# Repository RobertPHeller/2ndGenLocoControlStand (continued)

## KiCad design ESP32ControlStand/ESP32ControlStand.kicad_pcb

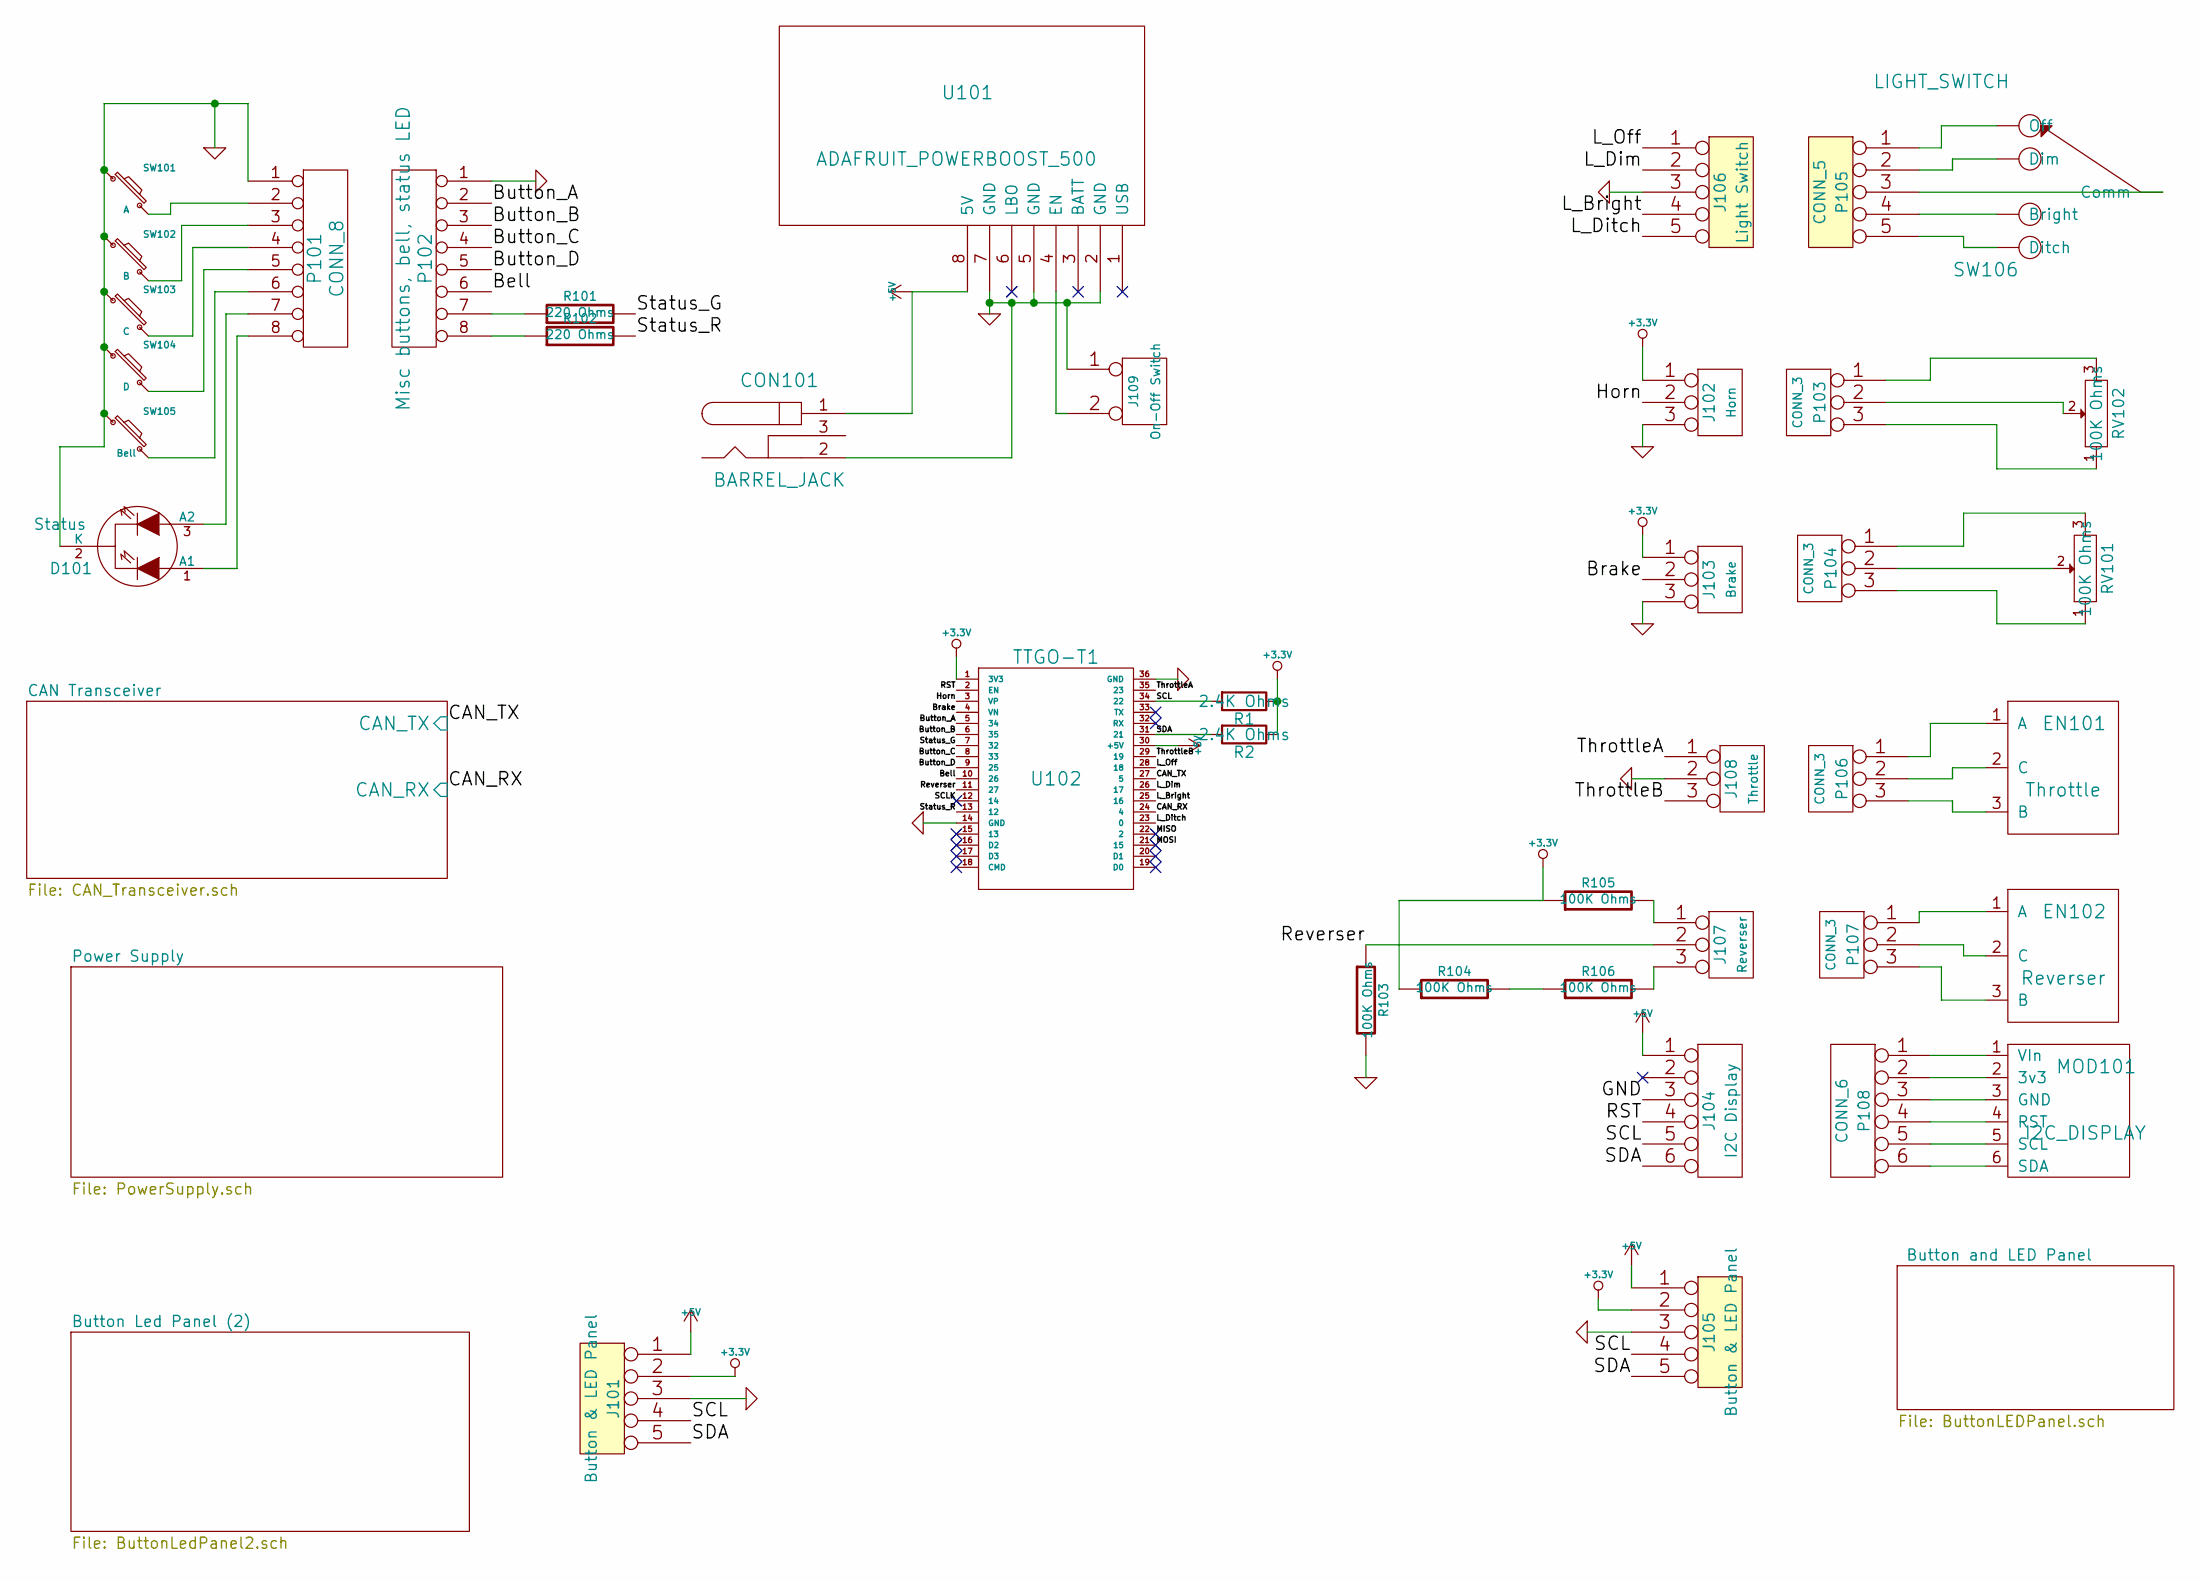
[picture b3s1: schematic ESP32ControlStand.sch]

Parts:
CON101: BARREL_JACK
D101: Status
EN101: Throttle; Mouser Part Number 706-25LB10-Q
EN102: Reverser; Mouser Part Number 652-PEC11R4325FN0012
J101, J105: Button & LED Panel
J102: Horn
J103: Brake
J104: I2C Display
J106: Light Switch
J107: Reverser
J108: Throttle
J109: On-Off Switch
MOD101: I2C_DISPLAY
P101: CONN_8
P102: Misc buttons, bell, status LED
P103, P104, P106, P107: CONN_3
P105: CONN_5
P108: CONN_6
R1, R2: 2.4K Ohms; R_Axial_DIN0207_L6.3mm_D2.5mm_P2.54mm_Vertical
R101, R102: 220 Ohms
R103, R104, R105, R106: 100K Ohms
RV101, RV102: 100K Ohms; Mouser Part Number 774-450T328F104A1A1
SW101: A
SW102: B
SW103: C
SW104: D
SW105: Bell
SW106: LIGHT_SWITCH
U101: ADAFRUIT_POWERBOOST_500
U102: TTGO-T1

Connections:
+3.3V: J101.2, J102.1, J103.1, J105.2, R1.1, R2.1, R104.1, R105.1, U102.1 (3V3); also elsewhere on the board
+5V: CON101.1, J101.1, J104.1, J105.1, U101.8 (5V), U102.30 (+5V); also elsewhere on the board
/Bell: P102.6, U102.10 (26)
/Brake: J103.2 (PM), U102.4 (VN)
/Button_A: P102.2, U102.5 (34)
/Button_B: P102.3, U102.6 (35)
/Button_C: P102.4, U102.8 (33)
/Button_D: P102.5, U102.9 (25)
/CAN_RX: U102.24 (4); also elsewhere on the board
/CAN_TX: U102.27 (5); also elsewhere on the board
/Horn: J102.2 (PM), U102.3 (VP)
/L_Bright: J106.4, U102.25 (16)
/L_Dim: J106.2, U102.26 (17)
/L_Ditch: J106.5, U102.23 (0)
/L_Off: J106.1, U102.28 (18)
/MISO: U102.22 (2)
/MOSI: U102.21 (15)
/RST: J104.4, U102.2 (EN)
/Reverser: J107.2 (PM), R103.1, U102.11 (27)
/SCL: J101.4, J104.5, J105.4, R1.2, U102.34 (22)
/SCLK: U102.12 (14)
/SDA: J101.5, J104.6, J105.5, R2.2, U102.31 (21)
/Status_G: R101.2, U102.7 (32)
/Status_R: R102.2, U102.13 (12)
/ThrottleA: J108.1, U102.35 (23)
/ThrottleB: J108.3, U102.29 (19)
GND: CON101.2, D101.2 (K), J101.3, J102.3, J103.3, J104.3, J105.3, J106.3, J108.2 (PM), J109.1, P101.1, P102.1, R103.2, SW101.1, SW102.1, SW103.1, SW104.1, SW105.1, U101.2 (GND), U101.5 (GND), U101.7 (GND), U102.14 (GND), U102.36 (GND); also elsewhere on the board
unnamed: D101.1 (A1), P101.8
unnamed: D101.3 (A2), P101.7
unnamed: EN101.1 (A), P106.1
unnamed: EN101.2 (C), P106.2 (PM)
unnamed: EN101.3 (B), P106.3
unnamed: EN102.1 (A), P107.1
unnamed: EN102.2 (C), P107.2 (PM)
unnamed: EN102.3 (B), P107.3
unnamed: J107.1, R105.2
unnamed: J107.3, R106.2
unnamed: J109.2 (PM), U101.4 (EN)
unnamed: MOD101.1 (VIn), P108.1
unnamed: MOD101.2 (3v3), P108.2
unnamed: MOD101.3 (GND), P108.3
unnamed: MOD101.4 (RST), P108.4
unnamed: MOD101.5 (SCL), P108.5
unnamed: MOD101.6 (SDA), P108.6
unnamed: P101.2, SW101.2
unnamed: P101.3, SW102.2
unnamed: P101.4, SW103.2
unnamed: P101.5, SW104.2
unnamed: P101.6, SW105.2
unnamed: P102.7, R101.1
unnamed: P102.8, R102.1
unnamed: P103.1, RV102.3
unnamed: P103.2 (PM), RV102.2
unnamed: P103.3, RV102.1
unnamed: P104.1, RV101.3
unnamed: P104.2 (PM), RV101.2
unnamed: P104.3, RV101.1
unnamed: P105.1, SW106.~
unnamed: P105.2, SW106.~
unnamed: P105.3, SW106.~
unnamed: P105.4, SW106.~
unnamed: P105.5, SW106.~
unnamed: R104.2, R106.1

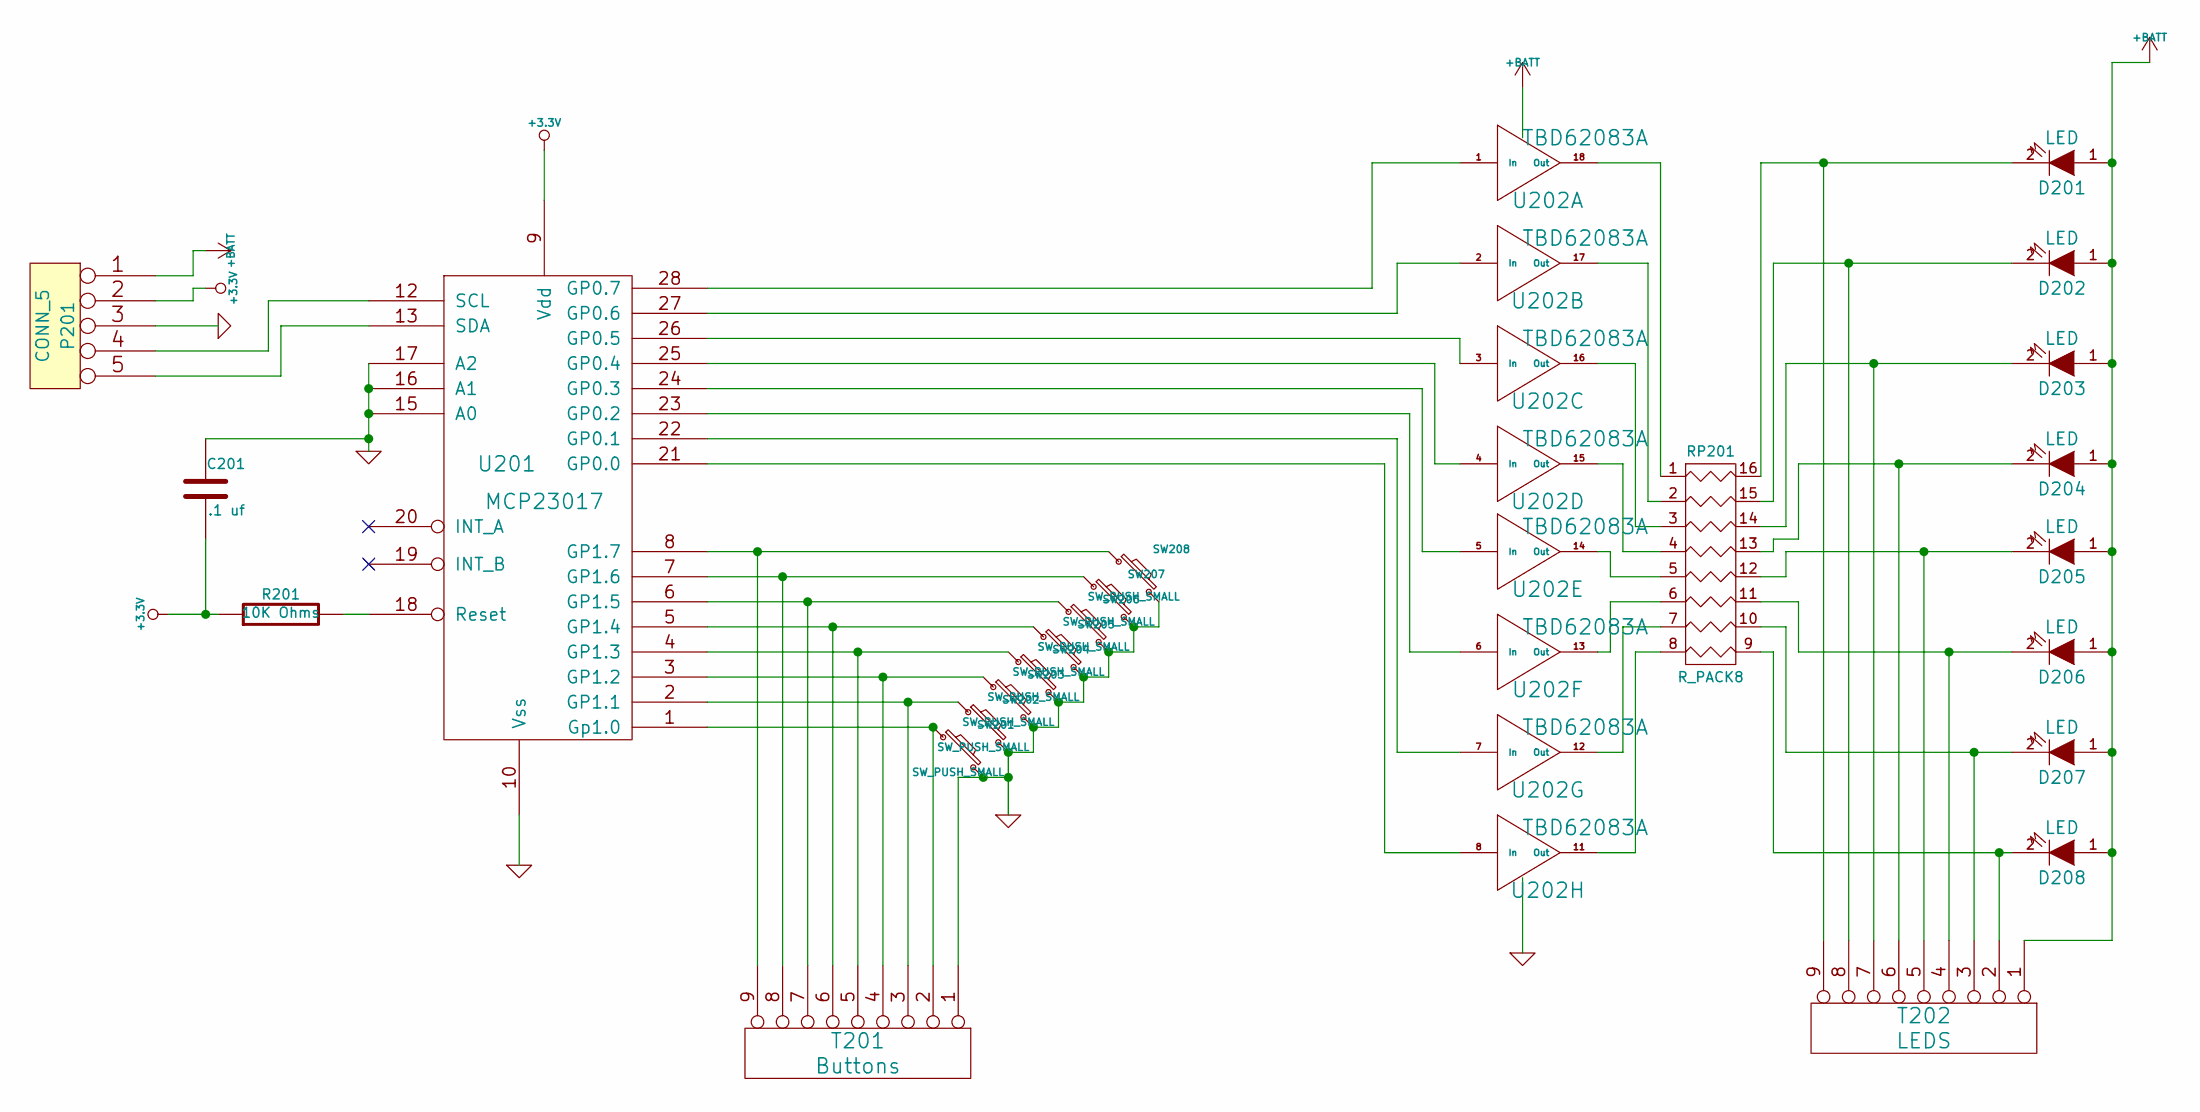
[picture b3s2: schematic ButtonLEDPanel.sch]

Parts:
C201: .1 uf
D201, D202, D203, D204, D205, D206, D207, D208: LED
P201: CONN_5
R201: 10K Ohms
RP201: R_PACK8
SW201, SW202, SW203, SW204, SW205, SW206, SW207, SW208: SW_PUSH_SMALL
T201: Buttons
T202: LEDS
U201: MCP23017
U202: TBD62083A

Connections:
+3.3V: C201.2, P201.2, R201.1, U201.9 (Vdd); also elsewhere on the board
+BATT: D201.1 (A), D202.1 (A), D203.1 (A), D204.1 (A), D205.1 (A), D206.1 (A), D207.1 (A), D208.1 (A), P201.1, T202.1, U202.10 (OC); also elsewhere on the board
GND: C201.1, P201.3, SW201.2, SW202.2, SW203.2, SW204.2, SW205.2, SW206.2, SW207.2, SW208.2, T201.1, U201.10 (Vss), U201.15 (A0), U201.16 (A1), U201.17 (A2), U202.9 (IC); also elsewhere on the board
unnamed: D201.2 (K), RP201.16 (R1), T202.9
unnamed: D202.2 (K), RP201.15 (R2), T202.8
unnamed: D203.2 (K), RP201.14 (R3), T202.7
unnamed: D204.2 (K), RP201.13 (R4), T202.6
unnamed: D205.2 (K), RP201.12 (R5), T202.5
unnamed: D206.2 (K), RP201.11 (R6), T202.4
unnamed: D207.2 (K), RP201.10 (R7), T202.3
unnamed: D208.2 (K), RP201.9 (R8), T202.2
unnamed: P201.4, U201.12 (SCL)
unnamed: P201.5, U201.13 (SDA)
unnamed: R201.2, U201.18 (Reset)
unnamed: RP201.1, U202.18 (Out)
unnamed: RP201.2, U202.17 (Out)
unnamed: RP201.3, U202.16 (Out)
unnamed: RP201.4, U202.15 (Out)
unnamed: RP201.5, U202.14 (Out)
unnamed: RP201.6, U202.13 (Out)
unnamed: RP201.7, U202.12 (Out)
unnamed: RP201.8, U202.11 (Out)
unnamed: SW201.1, T201.2, U201.1 (Gp1.0)
unnamed: SW202.1, T201.3, U201.2 (GP1.1)
unnamed: SW203.1, T201.4, U201.3 (GP1.2)
unnamed: SW204.1, T201.5, U201.4 (GP1.3)
unnamed: SW205.1, T201.6, U201.5 (GP1.4)
unnamed: SW206.1, T201.7, U201.6 (GP1.5)
unnamed: SW207.1, T201.8, U201.7 (GP1.6)
unnamed: SW208.1, T201.9, U201.8 (GP1.7)
unnamed: U201.21 (GP0.0), U202.8 (In)
unnamed: U201.22 (GP0.1), U202.7 (In)
unnamed: U201.23 (GP0.2), U202.6 (In)
unnamed: U201.24 (GP0.3), U202.5 (In)
unnamed: U201.25 (GP0.4), U202.4 (In)
unnamed: U201.26 (GP0.5), U202.3 (In)
unnamed: U201.27 (GP0.6), U202.2 (In)
unnamed: U201.28 (GP0.7), U202.1 (In)

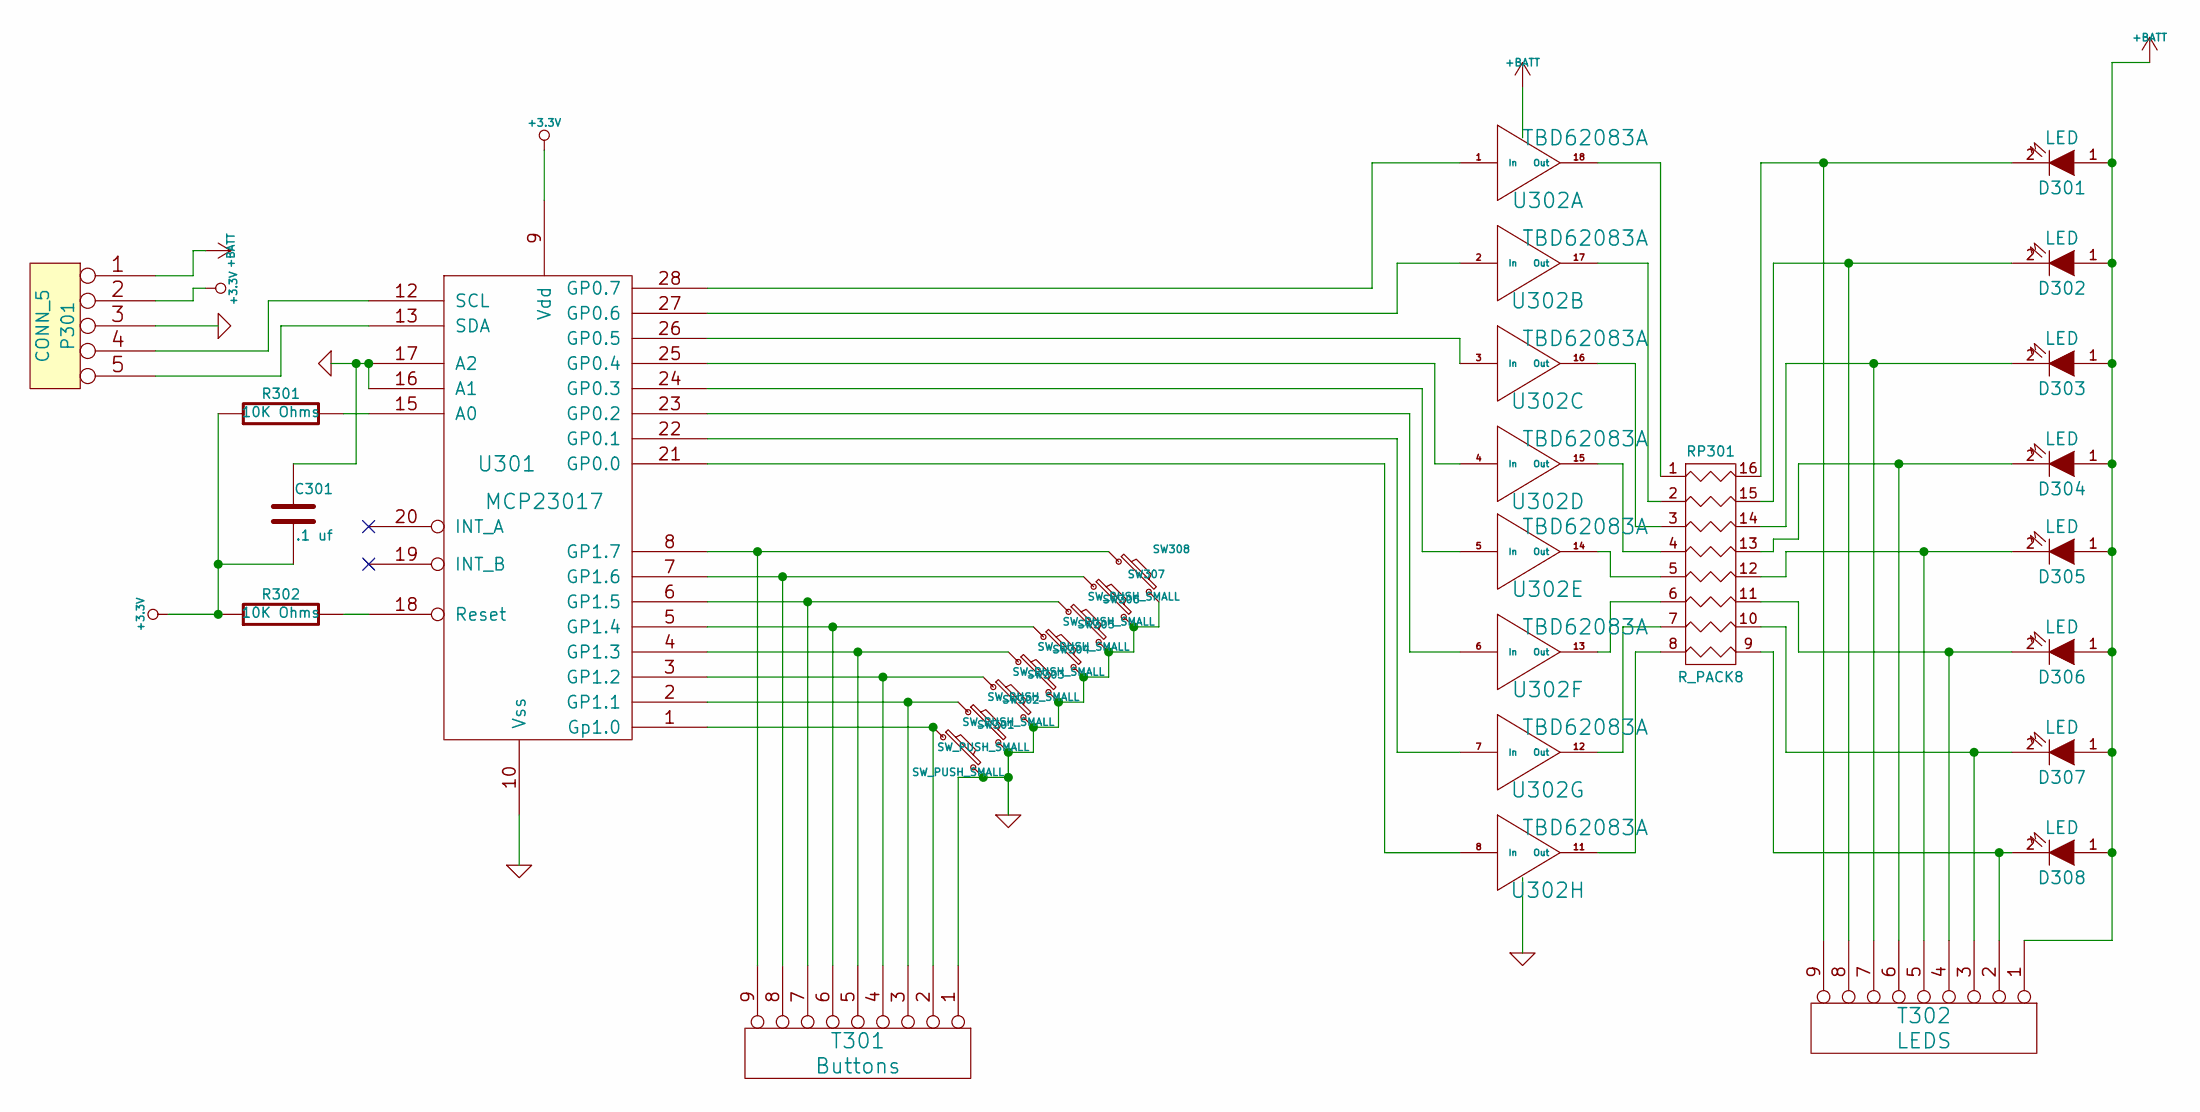
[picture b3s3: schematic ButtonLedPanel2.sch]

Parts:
C301: .1 uf
D301, D302, D303, D304, D305, D306, D307, D308: LED
P301: CONN_5
R301, R302: 10K Ohms
RP301: R_PACK8
SW301, SW302, SW303, SW304, SW305, SW306, SW307, SW308: SW_PUSH_SMALL
T301: Buttons
T302: LEDS
U301: MCP23017
U302: TBD62083A

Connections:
+3.3V: C301.2, P301.2, R301.1, R302.1, U301.9 (Vdd); also elsewhere on the board
+BATT: D301.1 (A), D302.1 (A), D303.1 (A), D304.1 (A), D305.1 (A), D306.1 (A), D307.1 (A), D308.1 (A), P301.1, T302.1, U302.10 (OC); also elsewhere on the board
GND: C301.1, P301.3, SW301.2, SW302.2, SW303.2, SW304.2, SW305.2, SW306.2, SW307.2, SW308.2, T301.1, U301.10 (Vss), U301.16 (A1), U301.17 (A2), U302.9 (IC); also elsewhere on the board
unnamed: D301.2 (K), RP301.16 (R1), T302.9
unnamed: D302.2 (K), RP301.15 (R2), T302.8
unnamed: D303.2 (K), RP301.14 (R3), T302.7
unnamed: D304.2 (K), RP301.13 (R4), T302.6
unnamed: D305.2 (K), RP301.12 (R5), T302.5
unnamed: D306.2 (K), RP301.11 (R6), T302.4
unnamed: D307.2 (K), RP301.10 (R7), T302.3
unnamed: D308.2 (K), RP301.9 (R8), T302.2
unnamed: P301.4, U301.12 (SCL)
unnamed: P301.5, U301.13 (SDA)
unnamed: R301.2, U301.15 (A0)
unnamed: R302.2, U301.18 (Reset)
unnamed: RP301.1, U302.18 (Out)
unnamed: RP301.2, U302.17 (Out)
unnamed: RP301.3, U302.16 (Out)
unnamed: RP301.4, U302.15 (Out)
unnamed: RP301.5, U302.14 (Out)
unnamed: RP301.6, U302.13 (Out)
unnamed: RP301.7, U302.12 (Out)
unnamed: RP301.8, U302.11 (Out)
unnamed: SW301.1, T301.2, U301.1 (Gp1.0)
unnamed: SW302.1, T301.3, U301.2 (GP1.1)
unnamed: SW303.1, T301.4, U301.3 (GP1.2)
unnamed: SW304.1, T301.5, U301.4 (GP1.3)
unnamed: SW305.1, T301.6, U301.5 (GP1.4)
unnamed: SW306.1, T301.7, U301.6 (GP1.5)
unnamed: SW307.1, T301.8, U301.7 (GP1.6)
unnamed: SW308.1, T301.9, U301.8 (GP1.7)
unnamed: U301.21 (GP0.0), U302.8 (In)
unnamed: U301.22 (GP0.1), U302.7 (In)
unnamed: U301.23 (GP0.2), U302.6 (In)
unnamed: U301.24 (GP0.3), U302.5 (In)
unnamed: U301.25 (GP0.4), U302.4 (In)
unnamed: U301.26 (GP0.5), U302.3 (In)
unnamed: U301.27 (GP0.6), U302.2 (In)
unnamed: U301.28 (GP0.7), U302.1 (In)

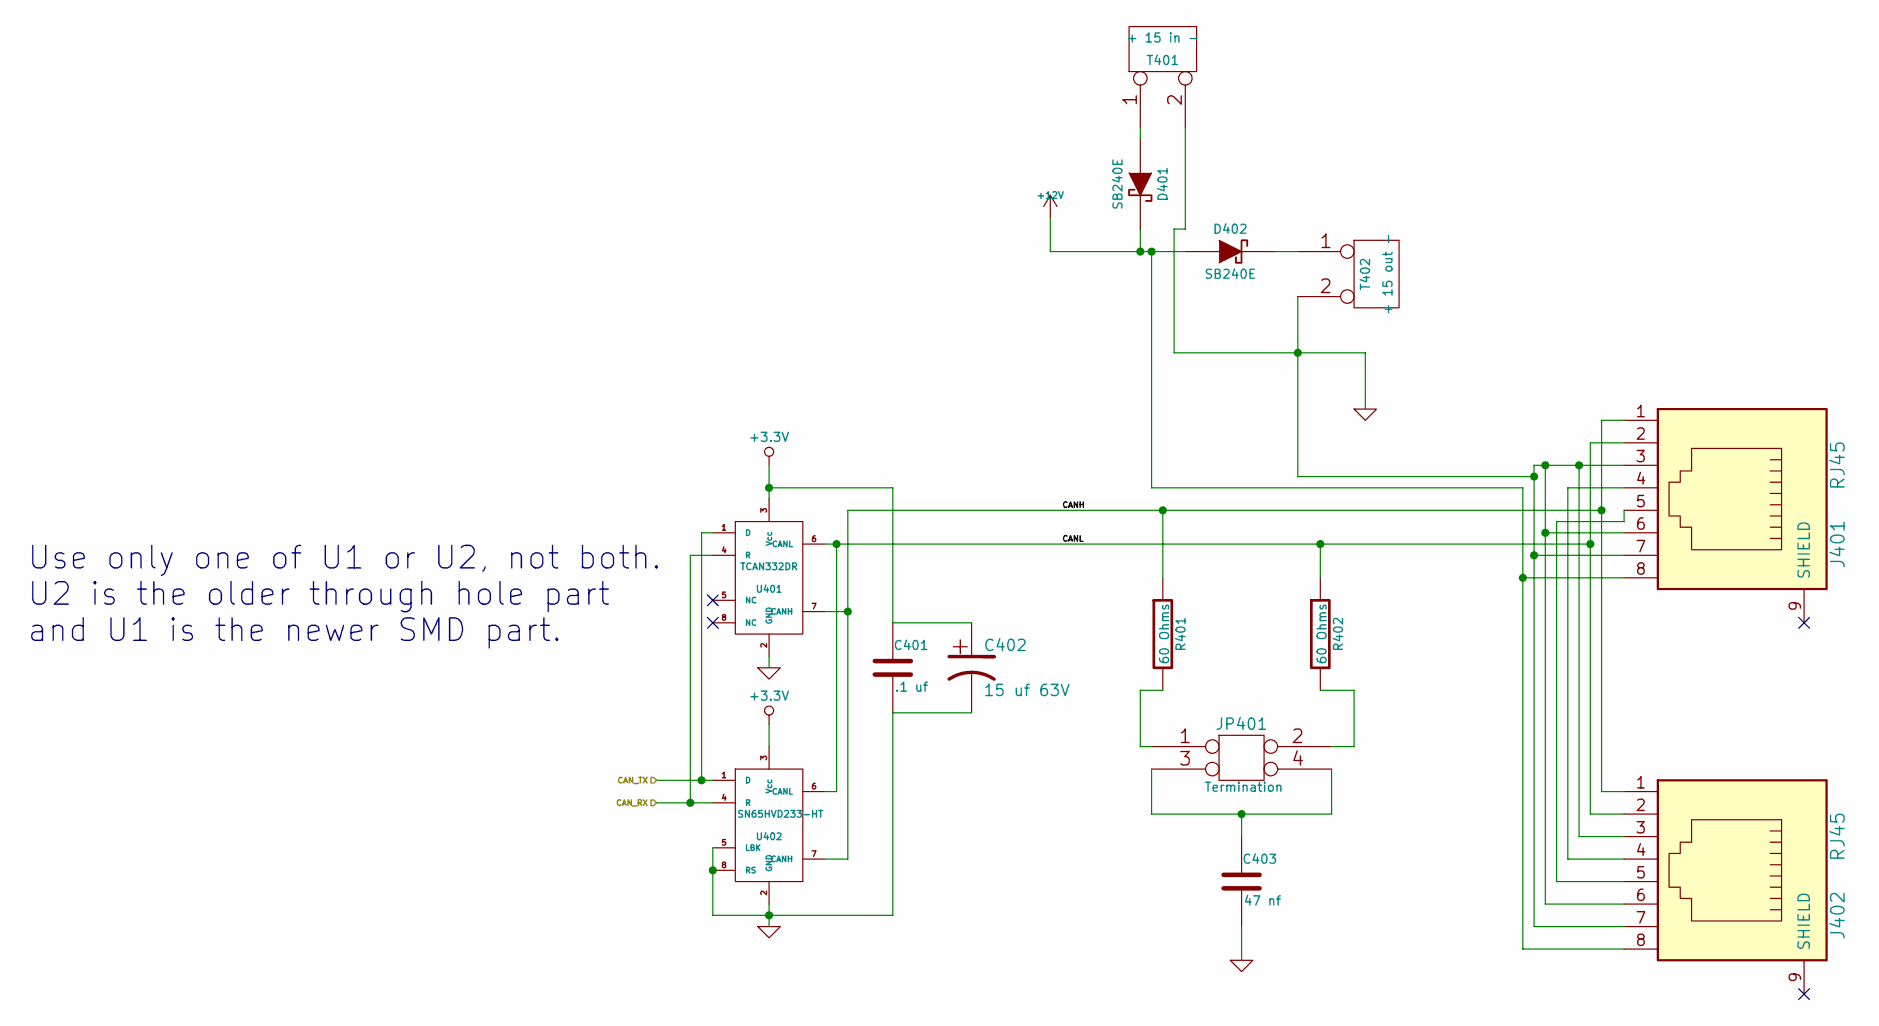
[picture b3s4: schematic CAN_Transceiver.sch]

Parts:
C401: .1 uf; Mouser Part Number 21RZ310-RC
C402: 15 uf 63V; Mouser Part Number 710-860080773002
C403: 47 nf; Mouser Part Number 75-1C10Z5U473M050B
D401, D402: SB240E; Mouser Part Number 625-SB240-E3
J401, J402: RJ45; Mouser Part Number 710-615008144221
JP401: Termination; Mouser Part Number 649-67997-404HLF
R401, R402: 60 Ohms; Mouser Part Number 71-RN60C60R0B/R
T401: + 15 in -; Mouser Part Number 651-1725656
T402: + 15 out -; Mouser Part Number 651-1725656
U401: TCAN332DR; Mouser Part Number 595-TCAN332DR
U402: SN65HVD233-HT; Mouser Part Number 595-SN65HVD233SJD

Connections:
+3.3V: C401.1, C402.1, U401.3 (Vcc), U402.3 (Vcc); also elsewhere on the board
+12V: D401.2 (K), D402.1 (A), J401.8, J402.8; also elsewhere on the board
/CAN Transceiver/CANH: J401.1, J402.1, R401.1, U401.7 (CANH), U402.7 (CANH)
/CAN Transceiver/CANL: J401.2, J402.2, R402.1, U401.6 (CANL), U402.6 (CANL)
/CAN_RX: U401.4 (R), U402.4 (R); also elsewhere on the board
/CAN_TX: U401.1 (D), U402.1 (D); also elsewhere on the board
GND: C401.2, C402.2, C403.2, J401.3, J401.6, J401.7, J402.3, J402.6, J402.7, T401.2 (PM), T402.2 (PM), U401.2 (GND), U402.2 (GND), U402.5 (LBK), U402.8 (RS); also elsewhere on the board
unnamed: C403.1, JP401.3, JP401.4
unnamed: D401.1 (A), T401.1
unnamed: D402.2 (K), T402.1
unnamed: J401.4, J402.4
unnamed: J401.5, J402.5
unnamed: JP401.1, R401.2
unnamed: JP401.2, R402.2

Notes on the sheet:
Use only one of U1 or U2, not both. U2 is the older through hole part and U1 is the newer SMD part.

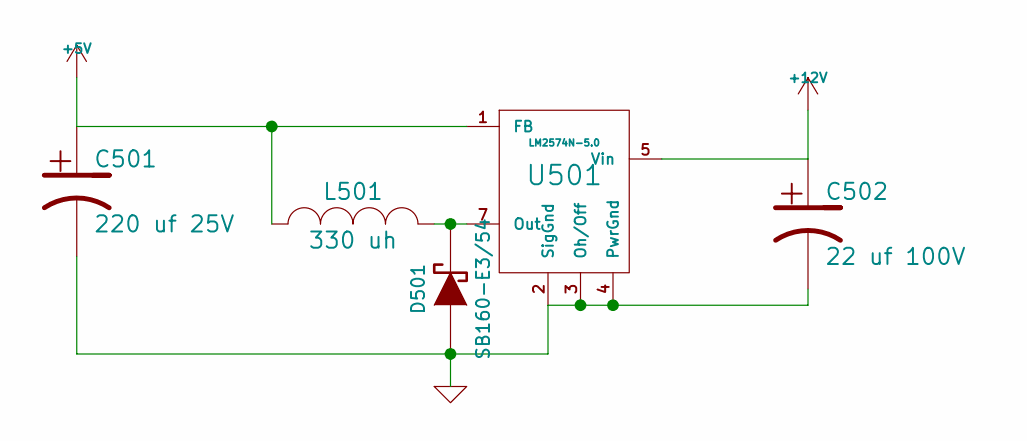
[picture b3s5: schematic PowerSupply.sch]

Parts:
C501: 220 uf 25V; Mouser Part Number 140-REA221M1EBK0811P
C502: 22 uf 100V; Mouser Part Number 140-REA220M2ABK0811P
D501: SB160-E3/54; Mouser Part Number 625-SB160-E3
L501: 330 uh; Mouser Part Number PE-52627NL
U501: LM2574N-5.0; Mouser Part Number 926-LM2574N-5.0/NOPB

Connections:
+5V: C501.1, L501.1, U501.1 (FB); also elsewhere on the board
+12V: C502.1, U501.5 (Vin); also elsewhere on the board
GND: C501.2, C502.2, D501.1 (A), U501.2 (SigGnd), U501.3 (Oh/Off), U501.4 (PwrGnd); also elsewhere on the board
unnamed: D501.2 (K), L501.2, U501.7 (Out)

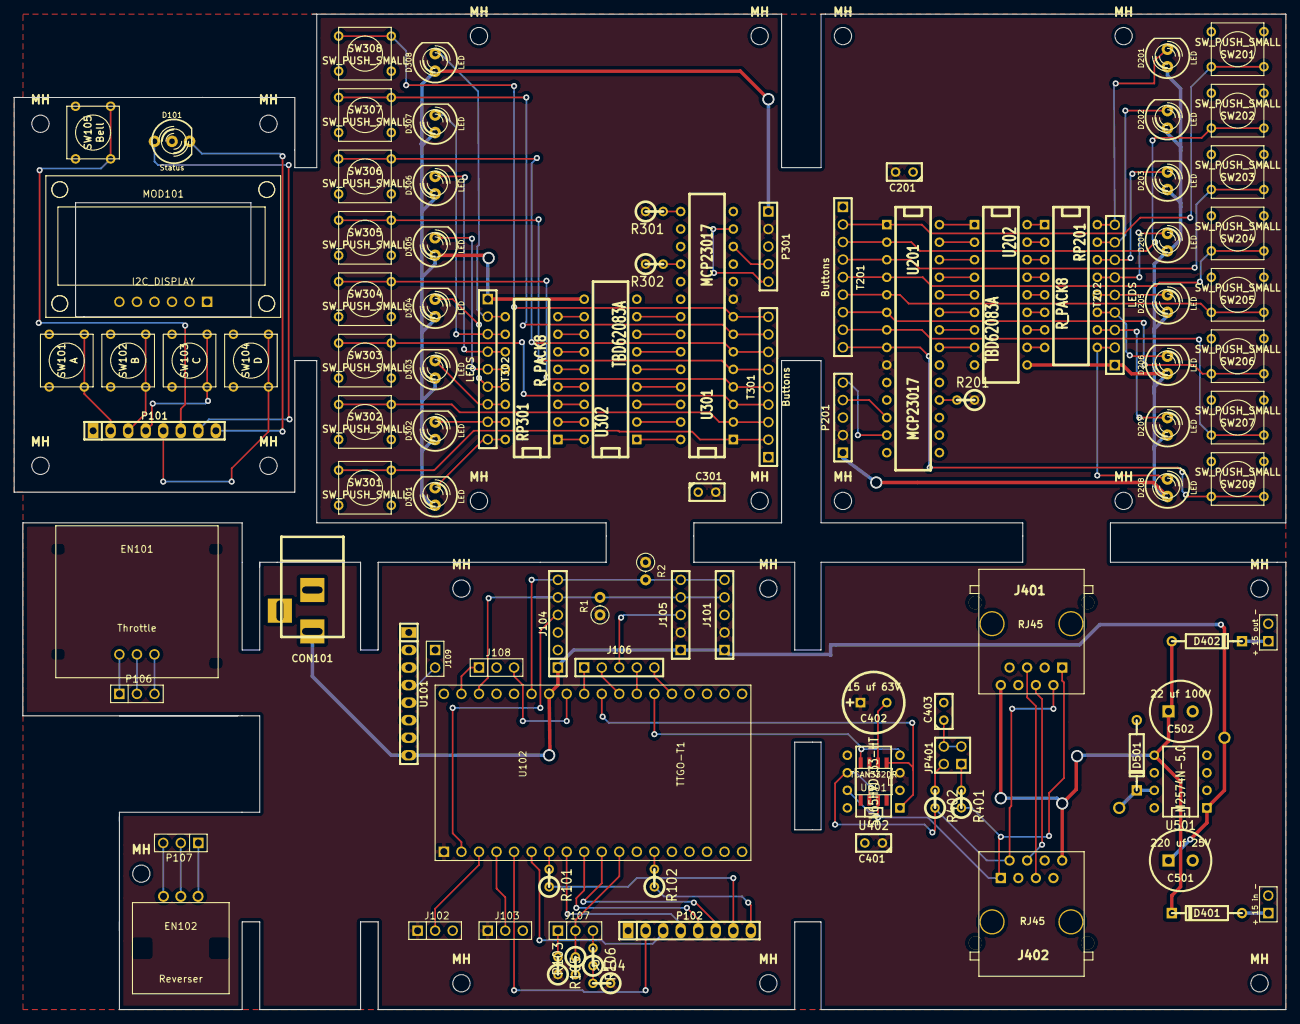
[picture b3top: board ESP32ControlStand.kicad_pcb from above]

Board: 2 copper layers, 184.1 x 144.1 mm, 120 parts (1 on the bottom side), 126 nets.

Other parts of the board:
MH: MountingHole_2-5mm_RevA_Date21Jun2010
MH#2, MH#3, MH#4, MH#5, MH#6, MH#7, MH#8, MH#9, MH#10, MH#11, MH#12, MH#13, MH#14, MH#15, MH#16, MH#17, MH#18, MH#19: MountingHole_2-5mm_RevA_Date21Jun2010

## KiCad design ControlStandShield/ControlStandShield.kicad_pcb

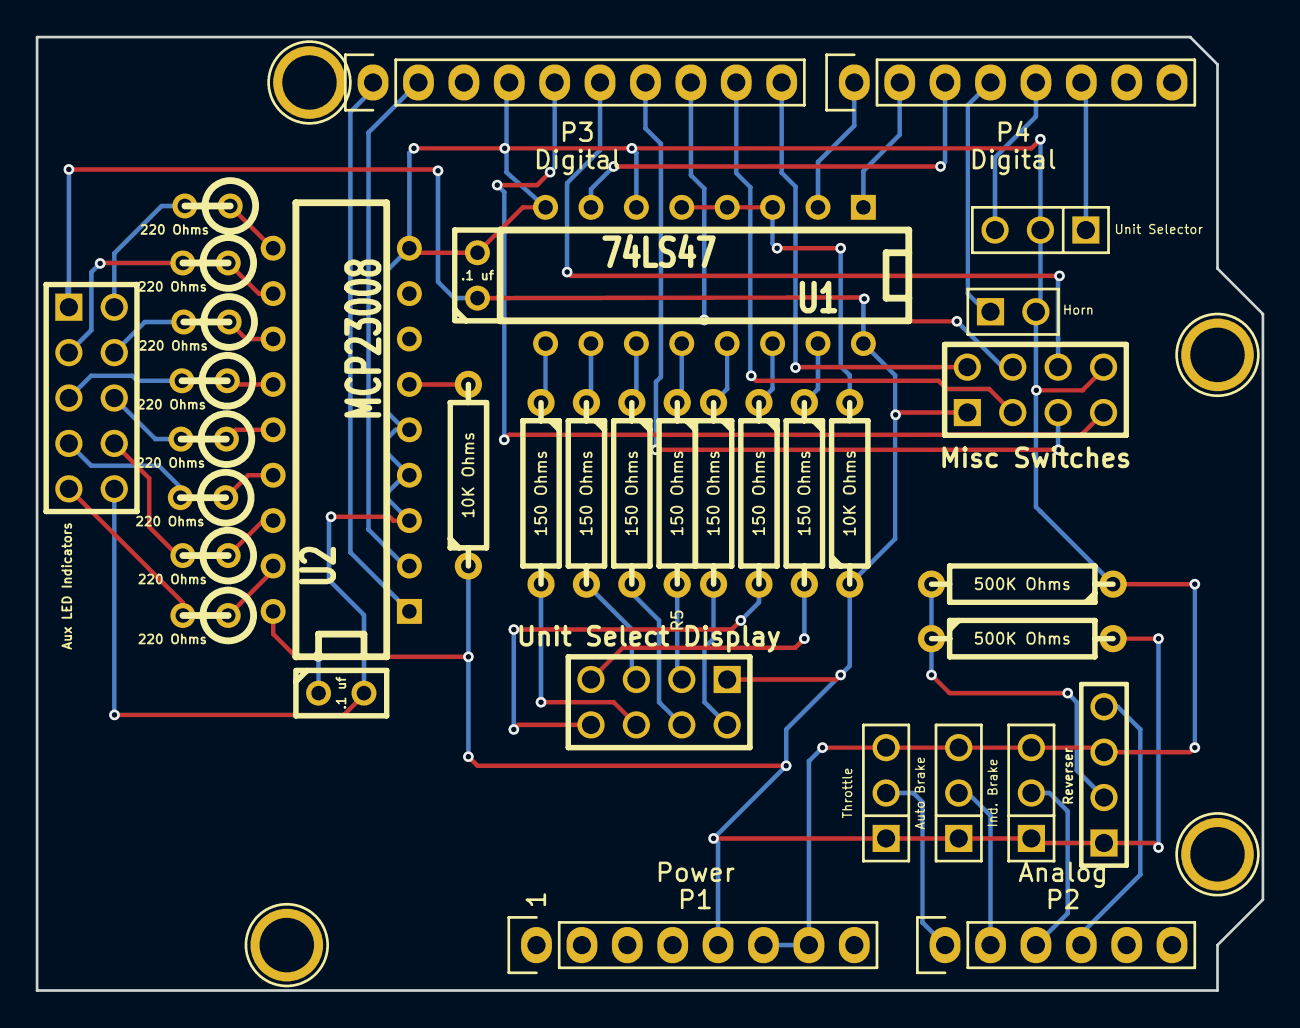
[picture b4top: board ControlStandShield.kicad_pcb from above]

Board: 2 copper layers, 68.6 x 53.3 mm, 40 parts (0 on the bottom side), 53 nets.

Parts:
C1, C2: .1 uf; C1
K4: Throttle; PIN_ARRAY_3X1
K5: Auto Brake; PIN_ARRAY_3X1
K6: Ind. Brake; PIN_ARRAY_3X1
K8: Unit Selector; PIN_ARRAY_3X1
P1: Power; Socket_Strip_Arduino_1x08
P2: Analog; Socket_Strip_Arduino_1x06
P3: Digital; Socket_Strip_Arduino_1x10
P4: Digital; Socket_Strip_Arduino_1x08
P5, P6, P7, P8: CONN_01X01; Arduino_1pin
P10: Reverser; PIN_ARRAY_4x1
P12: Horn; PIN_ARRAY_2X1
P13: Unit Select Display; pin_array_4x2
P15: Aux LED Indicators; PIN_ARRAY_5x2
P18: Misc Switches; pin_array_4x2
R1, R2: 500K Ohms; R4
R3, R11: 10K Ohms; R4
R4, R5, R6, R7, R8, R9, R10: 150 Ohms; R4
R12, R13, R14, R15, R16, R17, R18, R19: 220 Ohms; R1
U1: 74LS47; DIP-16__300
U2: MCP23008; DIP-18__300

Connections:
+5V: C1.1, C2.1, K4.1, K5.1, K6.1, P1.5, P10.1, P13.1, P15.1, P18.1, R1.2, R3.1, R11.1, U1.16, U2.18
/A0: K4.2, P2.1
/A1: K5.2, P2.2
/A2: K6.2, P2.3
/A3: P2.4, P10.4
/A4(SDA): P3.2, U2.2
/A5(SCL): P3.1, U2.1
/D2: K8.1, P4.6
/D3: K8.3, P4.5
/D4: P4.4, P12.1
/D5: P4.3, U1.7
/D6: P4.2, U1.1
/D7: P4.1, U1.2
/D8: P3.10, P18.2
/D9: P3.9, P18.3
/D10: P3.8, P18.4
/D11: P3.7, P18.5
/D12: P3.6, P18.6
/D13: P3.5, P18.7
GND: C1.2, C2.2, K4.3, K5.3, K6.3, K8.2, P1.6, P1.7, P3.4, P10.3, P12.2, P15.10, P18.8, R2.1, U1.6, U1.8, U2.3, U2.4, U2.5, U2.9
unnamed: P13.5, R7.2
unnamed: P13.4, R6.2
unnamed: P13.3, R5.2
unnamed: P13.2, R4.2
unnamed: R10.1, U1.14
unnamed: R8.1, U1.9
unnamed: R7.1, U1.10
unnamed: R6.1, U1.11
unnamed: R5.1, U1.12
unnamed: R4.1, U1.13
unnamed: R9.1, U1.15
unnamed: P13.8, R10.2
unnamed: P13.7, R9.2
unnamed: P13.6, R8.2
unnamed: P10.2, R1.1, R2.2
unnamed: P15.9, R19.2
unnamed: R19.1, U2.17
unnamed: P15.8, R18.2
unnamed: R18.1, U2.16
unnamed: P15.7, R17.2
unnamed: R17.1, U2.15
unnamed: P15.6, R16.2
unnamed: R16.1, U2.14
unnamed: P15.5, R15.2
unnamed: R15.1, U2.13
unnamed: P15.4, R14.2
unnamed: R14.1, U2.12
unnamed: P15.3, R13.2
unnamed: R13.1, U2.11
unnamed: P15.2, R12.2
unnamed: R12.1, U2.10
unnamed: R11.2, U2.6
unnamed: R3.2, U1.3, U1.4, U1.5

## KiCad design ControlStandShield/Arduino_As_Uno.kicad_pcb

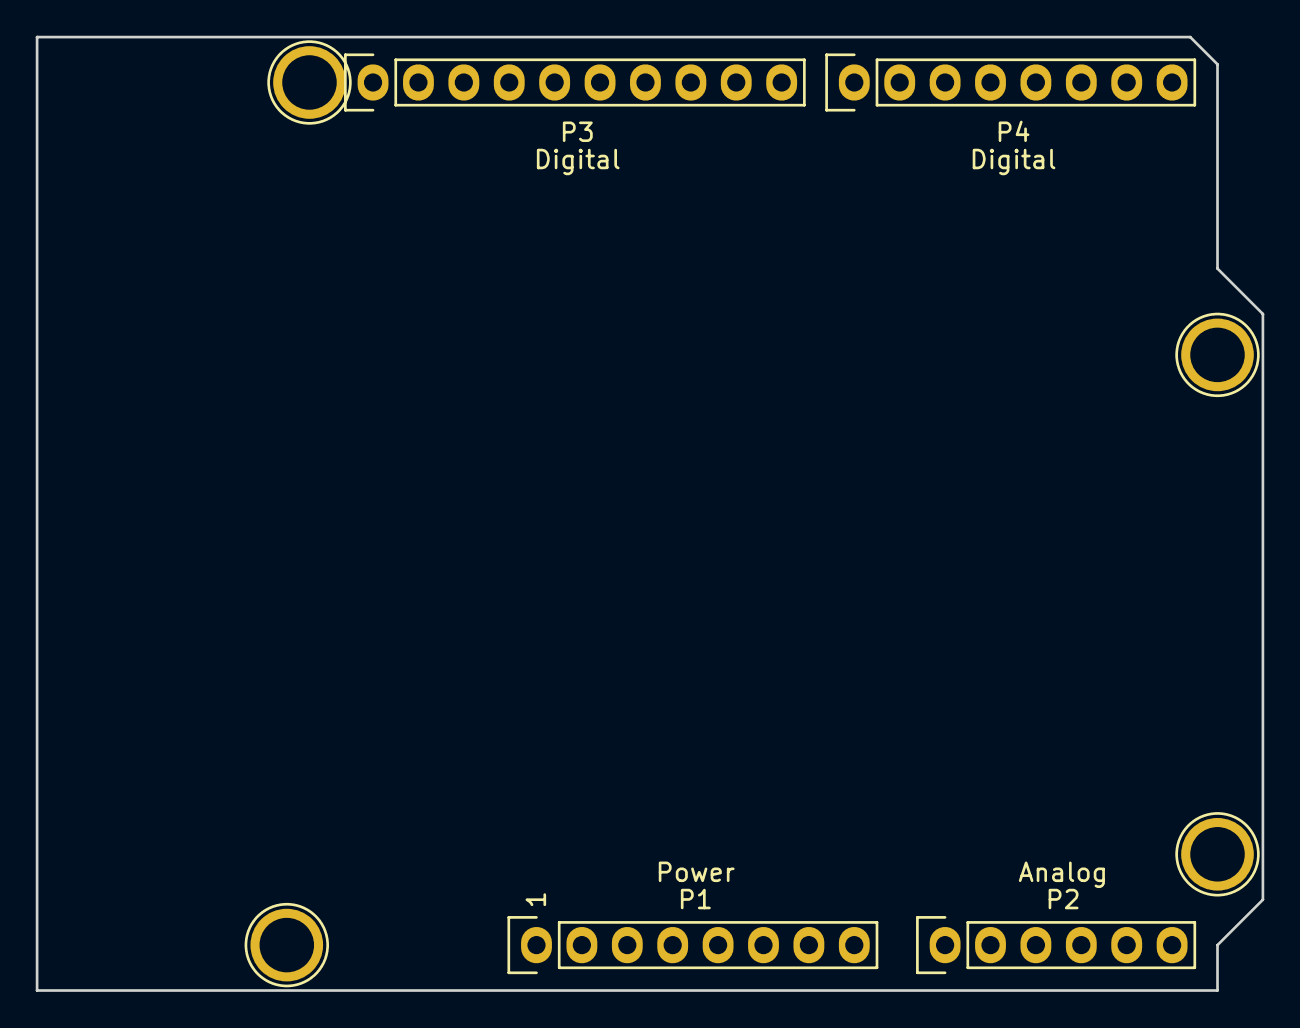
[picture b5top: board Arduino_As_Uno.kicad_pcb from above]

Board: 2 copper layers, 68.6 x 53.3 mm, 8 parts (0 on the bottom side), 3 nets, no tracks yet.

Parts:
P1: Power; Socket_Strip_Arduino_1x08
P2: Analog; Socket_Strip_Arduino_1x06
P3: Digital; Socket_Strip_Arduino_1x10
P4: Digital; Socket_Strip_Arduino_1x08
P5, P6, P7, P8: CONN_01X01; Arduino_1pin

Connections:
/A4(SDA): P2.5, P3.2
/A5(SCL): P2.6, P3.1
GND: P1.6, P1.7, P3.4
